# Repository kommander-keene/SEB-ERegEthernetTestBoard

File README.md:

# SEB-ERegEthernetTestBoard
Test board for ethernet test

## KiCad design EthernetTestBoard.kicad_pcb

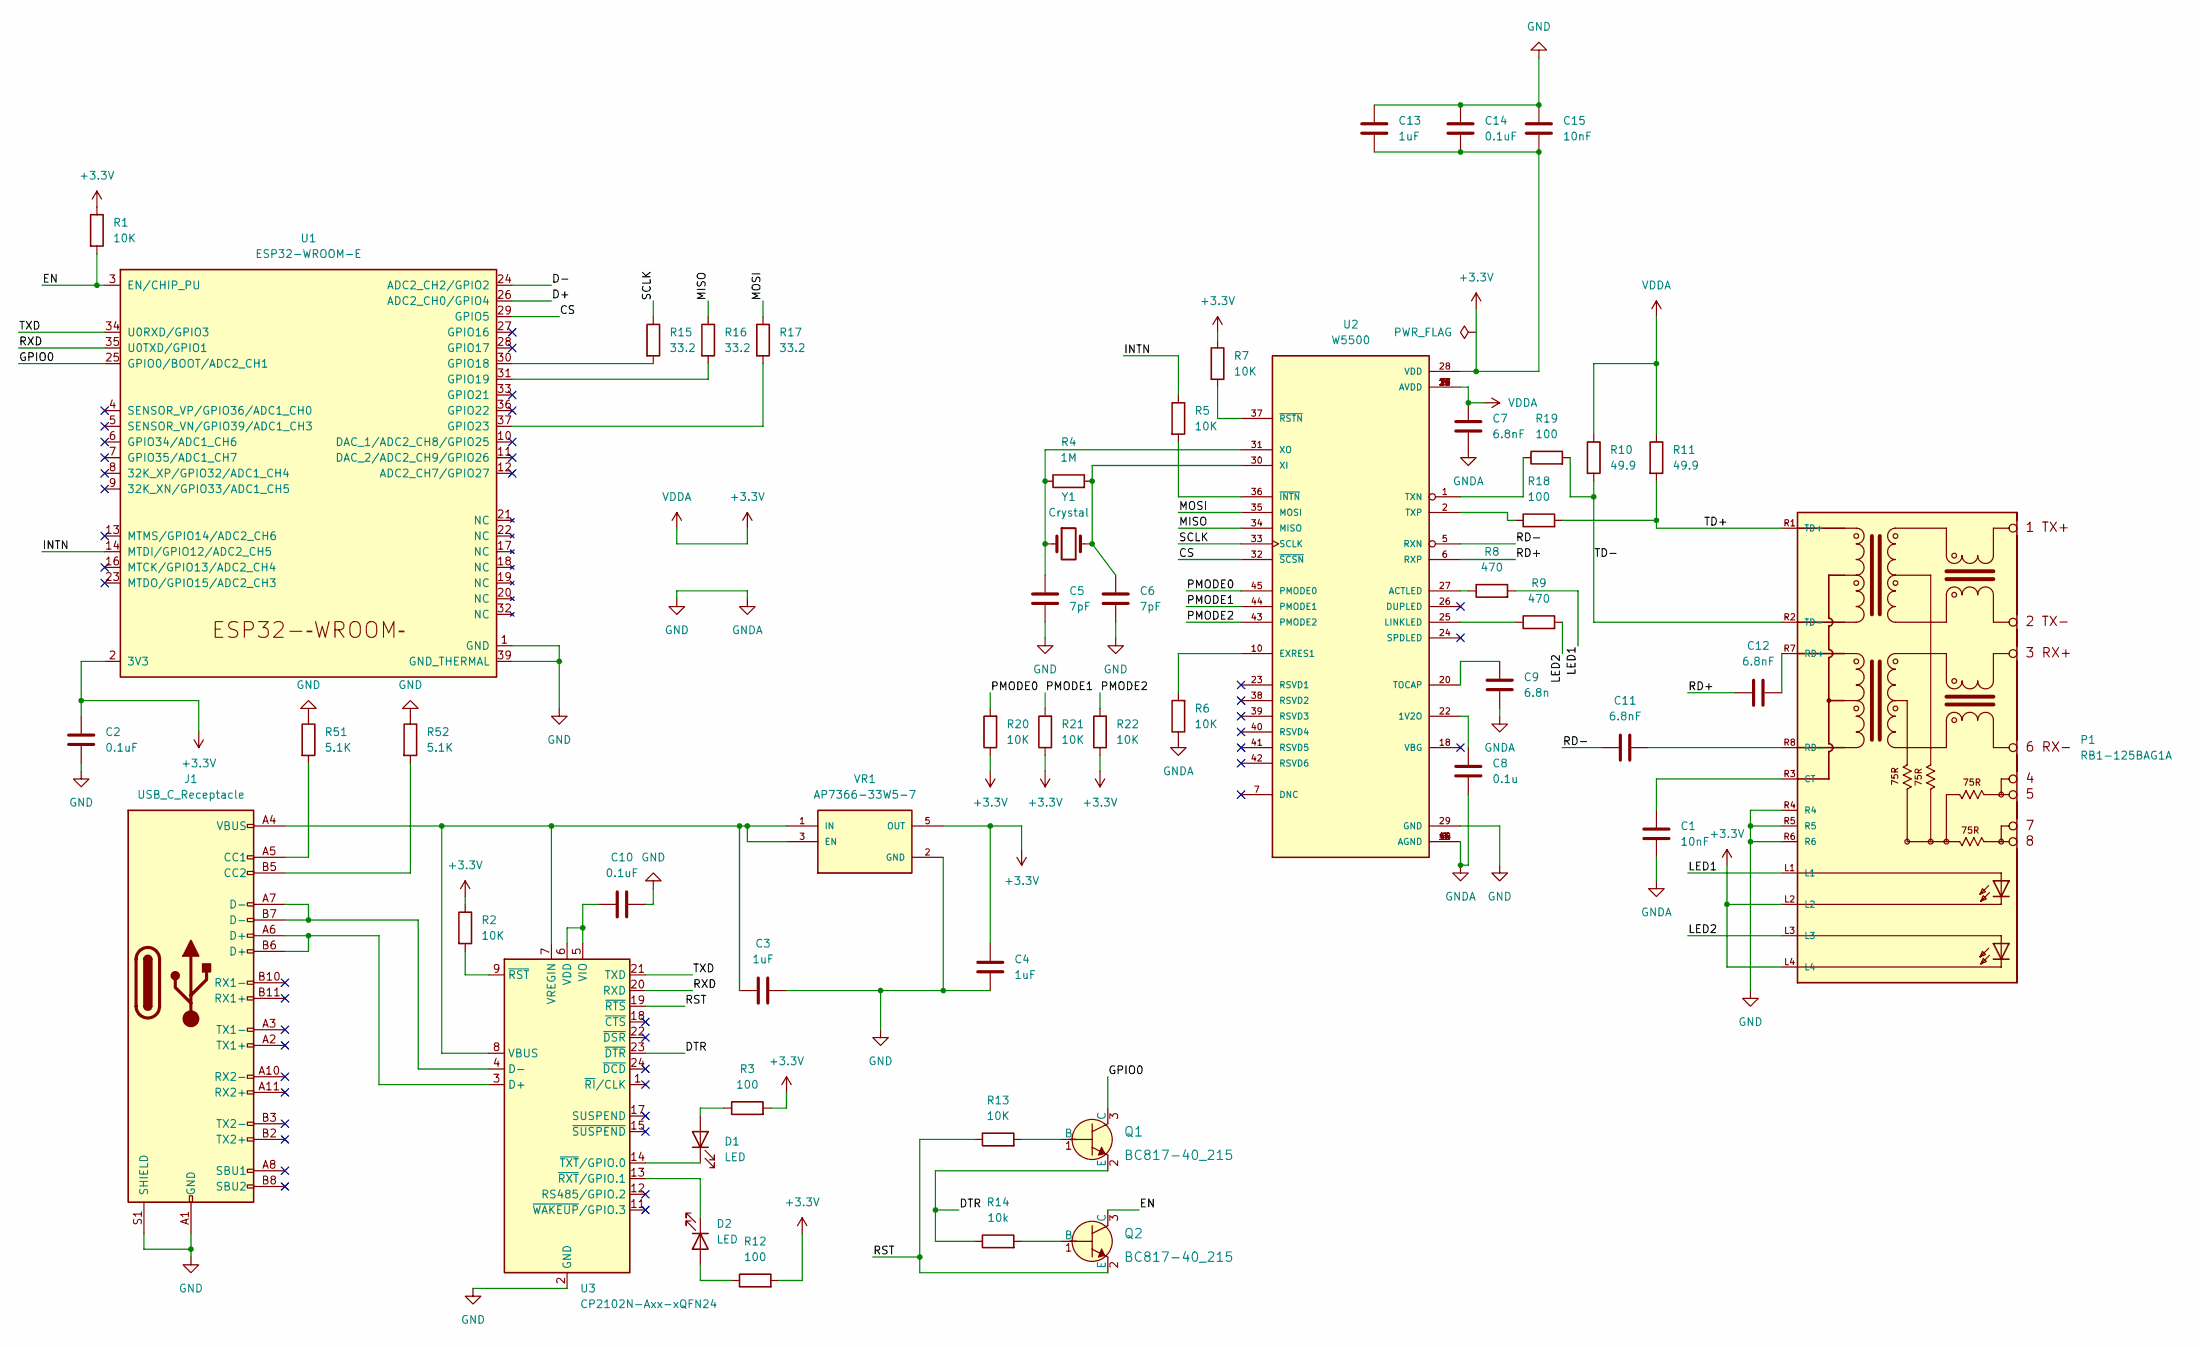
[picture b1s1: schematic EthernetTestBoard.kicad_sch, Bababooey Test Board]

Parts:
C1: 10nF; C_0603_1608Metric_Pad1.08x0.95mm_HandSolder
C2, C10: 0.1uF; C_0603_1608Metric_Pad1.08x0.95mm_HandSolder
C3, C4: 1uF; C_0603_1608Metric_Pad1.08x0.95mm_HandSolder
C5, C6: 7pF; C_0805_2012Metric_Pad1.18x1.45mm_HandSolder
C7, C11, C12: 6.8nF; C_1812_4532Metric_Pad1.57x3.40mm_HandSolder
C8: 0.1u; C_0603_1608Metric_Pad1.08x0.95mm_HandSolder
C9: 6.8n; C_1812_4532Metric_Pad1.57x3.40mm_HandSolder
C13: 1uF; C_1812_4532Metric_Pad1.57x3.40mm_HandSolder
C14: 0.1uF; C_1812_4532Metric_Pad1.57x3.40mm_HandSolder
C15: 10nF; C_1812_4532Metric_Pad1.57x3.40mm_HandSolder
D1, D2: LED; LED_0603_1608Metric
J1: USB_C_Receptacle; MOLEX_2012670005
P1: RB1-125BAG1A; WIZNET_RB1-125BAG1A
Q1, Q2: BC817-40_215; SOT95P230X110-3N; MPN BC817-40,215; Digi-Key_PN 1727-2919-1-ND
R1, R2, R13: 10K; C_0805_2012Metric_Pad1.18x1.45mm_HandSolder
R3, R12, R18, R19: 100; C_0603_1608Metric_Pad1.08x0.95mm_HandSolder
R4: 1M; C_0603_1608Metric_Pad1.08x0.95mm_HandSolder
R5, R6, R7, R20, R21, R22: 10K; R_0805_2012Metric_Pad1.20x1.40mm_HandSolder
R8, R9: 470; C_0603_1608Metric_Pad1.08x0.95mm_HandSolder
R10, R11: 49.9; C_0603_1608Metric_Pad1.08x0.95mm_HandSolder
R14: 10k; C_0805_2012Metric_Pad1.18x1.45mm_HandSolder
R15, R16, R17: 33.2; C_0805_2012Metric_Pad1.18x1.45mm_HandSolder
R51, R52: 5.1K; C_0805_2012Metric_Pad1.18x1.45mm_HandSolder
U1: ESP32-WROOM-E; ESP32-WROOM-32E
U2: W5500; QFP50P900X900X160-48N
U3: CP2102N-Axx-xQFN24; QFN50P400X400X80-25N
VR1: AP7366-33W5-7; SOT95P285X140-5N; PARTREV 1-2
Y1: Crystal; XTAL_ECS-250-18-23A-EN-TR

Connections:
+3V3: C2.1, C4.2, C7.1, C13.2, C14.2, C15.2, P1.L2, P1.L4, R1.1, R2.1, R3.2, R7.1, R10.1, R11.1, R12.2, R20.1, R21.1, R22.1, U1.2 (3V3), U2.4 (AVDD), U2.8 (AVDD), U2.11 (AVDD), U2.15 (AVDD), U2.17 (AVDD), U2.21 (AVDD), U2.28 (VDD), VR1.5 (OUT)
/CS: U1.29 (GPIO5), U2.32 (~SCSN)
/D+: U1.26 (ADC2_CH0/GPIO4)
/D-: U1.24 (ADC2_CH2/GPIO2)
/DTR: Q1.2 (E), R14.1, U3.23 (~DTR)
/EN: Q2.3 (C), R1.2, U1.3 (EN/CHIP_PU)
/GPIO0: Q1.3 (C), U1.25 (GPIO0/BOOT/ADC2_CH1)
/INTN: R5.1, U1.14 (MTDI/GPIO12/ADC2_CH5)
/LED1: P1.L1, R8.2
/LED2: P1.L3, R9.2
/MISO: R16.1, U2.34 (MISO)
/MOSI: R17.1, U2.35 (MOSI)
/PMODE0: R20.2, U2.45 (PMODE0)
/PMODE1: R21.2, U2.44 (PMODE1)
/PMODE2: R22.2, U2.43 (PMODE2)
/RD+: C12.2, U2.6 (RXP)
/RD-: C11.2, U2.5 (RXN)
/RST: Q2.2 (E), R13.1, U3.19 (~RTS)
/RXD: U1.35 (U0TXD/GPIO1), U3.20 (RXD)
/SCLK: R15.1, U2.33 (SCLK)
/TD+: P1.R1 (TD+), R11.2, R18.2
/TD-: P1.R2 (TD-), R10.2, R19.2
/TXD: U1.34 (U0RXD/GPIO3), U3.21 (TXD)
GND: C1.2, C2.2, C3.2, C4.1, C5.2, C6.2, C7.2, C8.2, C9.2, C10.2, C13.1, C14.1, C15.1, J1.A1 (GND), J1.A12 (GND), J1.B1 (GND), J1.B12 (GND), J1.S1 (SHIELD), P1.R4, P1.R5, P1.R6, R6.1, R51.1, R52.1, U1.1 (GND), U1.15 (GND), U1.38 (GND), U1.39 (GND_THERMAL), U2.3 (AGND), U2.9 (AGND), U2.14 (AGND), U2.16 (AGND), U2.19 (AGND), U2.29 (GND), U2.48 (AGND), U3.2 (GND), U3.25 (GND), VR1.2 (GND)
unnamed: C1.1, P1.R3 (CT)
unnamed: C3.1, J1.A4 (VBUS), J1.A9 (VBUS), J1.B4 (VBUS), J1.B9 (VBUS), U3.7 (VREGIN), U3.8 (VBUS), VR1.1 (IN), VR1.3 (EN)
unnamed: C5.1, R4.1, U2.31 (XO), Y1.1
unnamed: C6.1, R4.2, U2.30 (XI), Y1.2
unnamed: C8.1, U2.22 (1V2O)
unnamed: C9.1, U2.20 (TOCAP)
unnamed: C11.1, P1.R8 (RD-)
unnamed: C12.1, P1.R7 (RD+)
unnamed: D1.1 (K), U3.14 (~TXT/GPIO.0)
unnamed: D1.2 (A), R3.1
unnamed: D2.1 (K), U3.13 (~RXT/GPIO.1)
unnamed: D2.2 (A), R12.1
unnamed: J1.A5 (CC1), R51.2
unnamed: J1.A6 (D+), J1.B6 (D+), U3.3 (D+)
unnamed: J1.A7 (D-), J1.B7 (D-), U3.4 (D-)
unnamed: J1.B5 (CC2), R52.2
unnamed: Q1.1 (B), R13.2
unnamed: Q2.1 (B), R14.2
unnamed: R2.2, U3.9 (~RST)
unnamed: R6.2, U2.10 (EXRES1)
unnamed: R7.2, U2.37 (~RSTN)
unnamed: R8.1, U2.27 (ACTLED)
unnamed: R9.1, U2.25 (LINKLED)
unnamed: R15.2, U1.30 (GPIO18)
unnamed: R16.2, U1.31 (GPIO19)
unnamed: R17.2, U1.37 (GPIO23)
unnamed: R18.1, U2.2 (TXP)
unnamed: R19.1, U2.1 (TXN)
unnamed: R5.2, U2.36 (~INTN)
unnamed: C10.1, U3.5 (VIO), U3.6 (VDD)

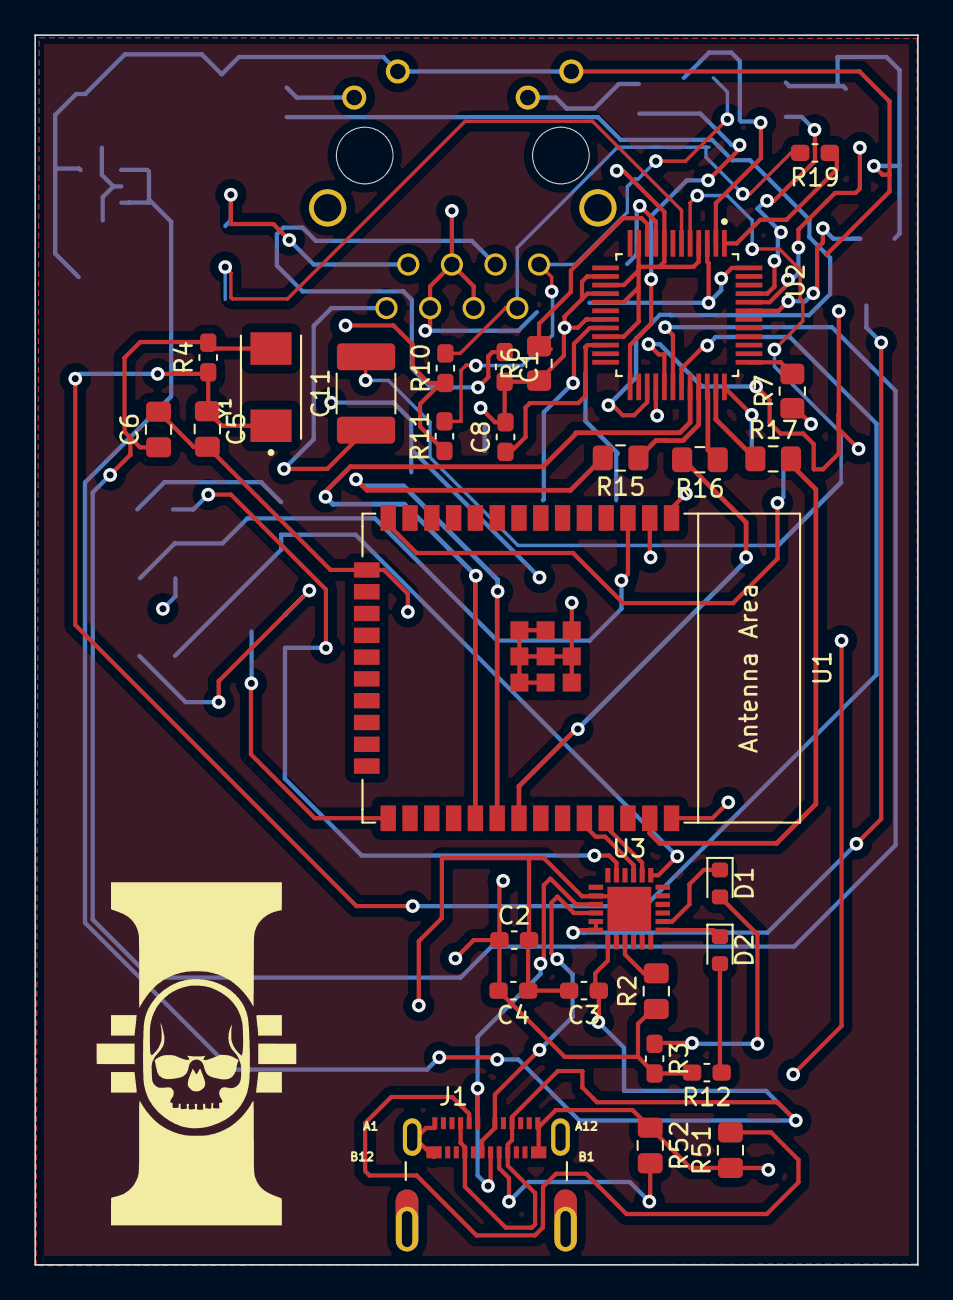
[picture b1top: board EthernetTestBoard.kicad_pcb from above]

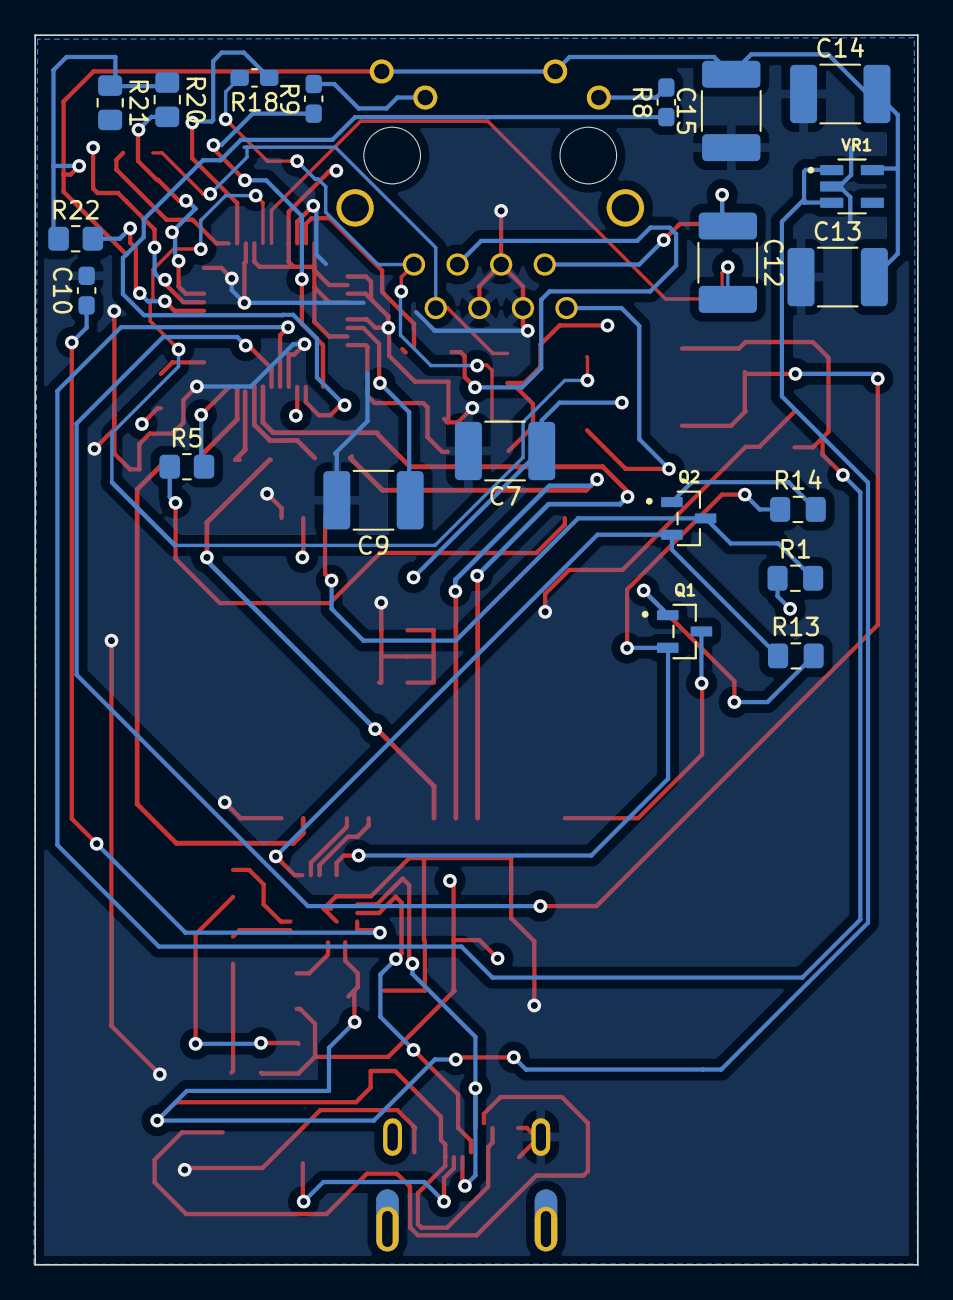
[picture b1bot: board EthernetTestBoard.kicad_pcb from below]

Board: 4 copper layers, 51.4 x 71.7 mm, 51 parts (20 on the bottom side), 52 nets.

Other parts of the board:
    : LOGO; actual footprint

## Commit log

2022-11-20 ereg test
2022-11-23 impedance matching match match
2022-11-26 about to push
2022-11-27 lemme go home
